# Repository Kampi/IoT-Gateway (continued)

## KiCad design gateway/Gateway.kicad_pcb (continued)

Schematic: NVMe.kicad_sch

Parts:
C1501, C1502, C1511: 10u; C_0805_2012Metric; mouser# 581-KGM21FS61E106KU
C1503, C1505, C1508, C1509: 100n; C_0805_2012Metric; mouser# 581-08055C104K4Z4A
C1504: 68n; C_0805_2012Metric; mouser# 581-08055C683K4T4A
C1506: 150p; C_0805_2012Metric; mouser# 581-08051U151JAT2A
C1507: 470u; CP_Elec_6.3x7.7; mouser# 667-EEE-FNJ471XUL
C1510: 33p; C_0805_2012Metric; mouser# 581-08053C330KAT2A
D1501: STPS3L60U; D_SMB; mouser# 511-STPS3L60U
H1501: Spacer; 9774025151R; mouser# 710-9774025151R
IC1501: ST1S14PHR; HSOP-8-1EP_3.9x4.9mm_P1.27mm_EP2.41x3.1mm; mouser# 511-ST1S14PHR
L1501: 10u; L_Wuerth_HCI-7050; mouser# 710-744314101
R1501, R1503: 100k; R_0805_2012Metric; mouser# 603-RT0805FRE13100KL
R1502: 100k; R_0805_2012Metric; mouser# 603-RT0805FRE13100KL; not fitted
R1504: 82k5; R_0805_2012Metric; mouser# 652-CR0805FX-8252ELF
R1505: 48k7; R_0805_2012Metric; mouser# 652-CR0805FX-4872ELF
R1506: 4k7; R_0805_2012Metric; mouser# 652-CR0805-JW-472ELF
TP1501, TP1502: TestPoint_Pad_1.0x1.0mm
X1501: SSD; MDT420M03001; mouser# 523-MDT420M03001

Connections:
+1V8: R1501.2, R1506.1; also elsewhere on the board
/Project Architecture/NVMe/PCIe.CLK_N: X1501.53 (REFCLKn); also elsewhere on the board
/Project Architecture/NVMe/PCIe.CLK_P: X1501.55 (REFCLKp); also elsewhere on the board
/Project Architecture/NVMe/PCIe.RX_N: X1501.41 (PERn0/SATA-B+); also elsewhere on the board
/Project Architecture/NVMe/PCIe.RX_P: X1501.43 (PERp0/SATA-B-); also elsewhere on the board
/Project Architecture/NVMe/PCIe.TX_N: X1501.47 (PETn0/SATA-A-); also elsewhere on the board
/Project Architecture/NVMe/PCIe.TX_P: X1501.49 (PETp0/SATA-A+); also elsewhere on the board
/Project Architecture/NVMe/PCIe.~CLK-REQ: X1501.50 (~PERST); also elsewhere on the board
/Project Architecture/NVMe/PCIe.~RST: X1501.52 (~CLKREQ); also elsewhere on the board
/Project Architecture/NVMe/SSD-Power-Enable: IC1501.5 (EN2), R1501.1, R1502.2; also elsewhere on the board
/Project Architecture/NVMe/V_{SSD}: C1506.1, C1507.1, C1508.1, C1509.1, C1510.1, C1511.1, L1501.2, R1504.1, TP1502.1 (1_1), X1501.2 (3.3V), X1501.4 (3.3V), X1501.12 (3.3V), X1501.14 (3.3V), X1501.16 (3.3V), X1501.18 (3.3V), X1501.70 (3.3V), X1501.72 (3.3V), X1501.74 (3.3V)
/Project Architecture/NVMe/~CTRL_WAKE1_MICO: R1506.2, X1501.54 (~PEWAKE); also elsewhere on the board
GND: C1501.2, C1502.2, C1503.2, C1504.2, C1507.2, C1508.2, C1509.2, C1510.2, C1511.2, D1501.2 (A), IC1501.6 (GND), IC1501.9 (EP), R1502.1, R1503.1, R1505.2, X1501.1 (GND), X1501.3 (GND), X1501.9 (GND), X1501.15 (GND), X1501.21 (GND), X1501.27 (GND), X1501.33 (GND), X1501.39 (GND), X1501.45 (GND), X1501.51 (GND), X1501.57 (GND), X1501.71 (GND), X1501.73 (GND), X1501.75 (GND); also elsewhere on the board
unnamed: C1505.2, D1501.1 (K), IC1501.8 (SW), L1501.1
unnamed: C1505.1, IC1501.1 (BOOT)
unnamed: C1506.2, IC1501.4 (FB), R1504.2, R1505.1, TP1501.1 (1_1)
unnamed: IC1501.3 (~EN1), R1503.2
V_{In}: C1501.1, C1502.1, C1503.1, C1504.1, IC1501.7 (VIN); also elsewhere on the board

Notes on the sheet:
[${#}] ${TITLE}
LAYOUT NOTE: Add support for the Key M 2230 standard.
LAYOUT NOTE: Place close to M.2 connector.
DESIGN NOTE: Selected for ~3.28 V.
DESIGN NOTE: Enabled by default.

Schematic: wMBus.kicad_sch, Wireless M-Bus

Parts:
AE1301: wM-Bus-Antenna
C1301, C1302: 1u; C_0805_2012Metric; mouser# 581-08053G105MAT2A
C1303, C1304: 100n; C_0805_2012Metric; mouser# 581-08055C104K4Z4A
IC1301: TLV75733PDBV; SOT-23-5; mouser# 595-TLV75733PDYDR
IC1302: 74LVC1G07; SOT-353_SC-70-5; mouser# 771-74LVC1G07GW-G
IC1303: TXB0102DCU; VSSOP-8_2.3x2mm_P0.5mm; mouser# 595-TXB0102DCUR
LED1301: wM-Bus; LED_0805_2012Metric; mouser# 749-SM0805YC
M1301: iM891A-XL
MP1301: SLP3-300-100-F; mouser# 749-SLP3-300-100-F
R1301: 10k; R_0805_2012Metric; mouser# 652-CR0805FX-1002ELF; not fitted
R1302: 68R; R_0805_2012Metric; mouser# 652-CR0805JW-680ELF
R1303, R1304, R1305, R1306: 0R; R_0805_2012Metric; mouser# 652-CR0805-J/-000ELF
R1307: 10k; R_0805_2012Metric; mouser# 652-CR0805FX-1002ELF
TP1301, TP1302, TP1303: TestPoint_Pad_1.0x1.0mm

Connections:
+1V8: C1303.1, IC1302.5 (VCC), IC1303.3 (VCCA), IC1303.6 (OE); also elsewhere on the board
+5V: C1301.2, IC1301.1 (IN); also elsewhere on the board
/Project Architecture/System on Module/wM-Bus-Power-Enable: IC1301.3 (EN), R1301.1, TP1301.1 (1_1); also elsewhere on the board
/Project Architecture/System on Module/wM-Bus.Reset: IC1302.2, TP1303.1 (1_1); also elsewhere on the board
/Project Architecture/System on Module/wM-Bus.RxD: R1303.1; also elsewhere on the board
/Project Architecture/System on Module/wM-Bus.TxD: R1304.1; also elsewhere on the board
/Project Architecture/wMBus/+3V3: C1302.2, C1304.1, IC1301.5 (OUT), IC1303.7 (VCCB), LED1301.2 (A), M1301.29 (VDD), R1307.1, TP1302.1 (1_1)
GND: C1301.1, C1302.1, C1303.2, C1304.2, IC1301.2 (GND), IC1302.3 (GND), IC1303.2 (GND), M1301.5 (GND), M1301.15 (GND), M1301.17 (GND), M1301.24 (GND), M1301.28 (GND), M1301.30 (GND), M1301.31 (GND), M1301.32 (GND), M1301.33 (GND), M1301.34 (GND), M1301.35 (GND), R1301.2, R1302.2; also elsewhere on the board
unnamed: IC1303.5 (A1), R1303.2
unnamed: IC1303.4 (A2), R1304.2
unnamed: IC1303.8 (B1), R1305.1
unnamed: IC1303.1 (B2), R1306.1
unnamed: LED1301.1 (K), R1302.1
unnamed: M1301.18 (RxD), R1306.2
unnamed: M1301.19 (TxD), R1305.2
unnamed: IC1302.4, M1301.25 (~RESET), R1307.2

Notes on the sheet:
[${#}] ${TITLE}
DESIGN NOTE: Use version with on-board antenna connector.
Power supply

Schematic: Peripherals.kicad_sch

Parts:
C1401: 100n; C_0805_2012Metric; mouser# 581-08055C104K4Z4A; not fitted
C1402, C1403, C1404, C1405, C1406, C1407, C1408, C1409, C1410: 100n; C_0805_2012Metric; mouser# 581-08055C104K4Z4A
IC1401: ATECC608B-SSHDA; SOIC-8_3.9x4.9mm_P1.27mm; mouser# 579-TECC608B-SSHDA-B; not fitted
IC1402: TUSB320; Texas_X2QFN-12_1.6x1.6mm_P0.4mm; mouser# 595-TUSB320LIRWBR
IC1403: TXS0108EPW; TSSOP-20_4.4x6.5mm_P0.65mm; mouser# 595-TXS0108EPWR
IC1404, IC1406: TXS0102DCU; VSSOP-8_2.3x2mm_P0.5mm; mouser# 595-TXS0102DCUR
IC1405: TXB0102DCU; VSSOP-8_2.3x2mm_P0.5mm; mouser# 595-TXB0102DCUR
R1401: 887k; R_0805_2012Metric; mouser# 652-CR0805FX-8873ELF
R1402: 1k8; R_0805_2012Metric; mouser# 652-CR0805JW-182ELF
R1403: 4k7; R_0805_2012Metric; mouser# 652-CR0805-JW-472ELF
R1404, R1405, R1406, R1407: 3k3; R_0805_2012Metric; mouser# 652-CR0805-JW-332ELF; not fitted
TP1401: TestPoint_Pad_1.0x1.0mm
X1401: OTG; USB4110; mouser# 640-USB4110-GF-A
X1402: GPIO; MSTBA_2,5_10-G-5,08_1x10_P5.08mm_Horizontal; mouser# 651-1757323; not fitted
X1403, X1405: I2C; MSTBA_2,5_4-G-5,08_1x04_P5.08mm_Horizontal; mouser# 651-1776524; not fitted
X1404: CAN; MSTBA_2,5_4-G-5,08_1x04_P5.08mm_Horizontal; mouser# 651-1776524; not fitted

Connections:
+1V8: C1403.1, C1405.1, C1406.1, C1407.1, IC1403.2 (VCCA), IC1403.10 (OE), IC1404.3 (VCCA), IC1404.6 (OE), IC1405.3 (VCCA), IC1405.6 (OE), IC1406.3 (VCCA), IC1406.6 (OE), R1403.1; also elsewhere on the board
+3V3: C1401.2, C1402.2, IC1401.8 (VCC), IC1402.12 (VDD); also elsewhere on the board
/Project Architecture/Battery/I2C.SCL: IC1401.6 (SCL), IC1404.4 (A2), IC1406.4 (A2); also elsewhere on the board
/Project Architecture/Battery/I2C.SDA: IC1401.5 (SDA), IC1404.5 (A1), IC1406.5 (A1); also elsewhere on the board
/Project Architecture/Peripherals/CAN.Rx: IC1405.4 (A2); also elsewhere on the board
/Project Architecture/Peripherals/CAN.Tx: IC1405.5 (A1); also elsewhere on the board
/Project Architecture/Peripherals/GPIO.Num0: IC1403.1 (A1); also elsewhere on the board
/Project Architecture/Peripherals/GPIO.Num1: IC1403.3 (A2); also elsewhere on the board
/Project Architecture/Peripherals/GPIO.Num2: IC1403.4 (A3); also elsewhere on the board
/Project Architecture/Peripherals/GPIO.Num3: IC1403.5 (A4); also elsewhere on the board
/Project Architecture/Peripherals/GPIO.Num4: IC1403.6 (A5); also elsewhere on the board
/Project Architecture/Peripherals/GPIO.Num5: IC1403.7 (A6); also elsewhere on the board
/Project Architecture/Peripherals/GPIO.Num6: IC1403.8 (A7); also elsewhere on the board
/Project Architecture/Peripherals/GPIO.Num7: IC1403.9 (A8); also elsewhere on the board
/Project Architecture/Peripherals/USB.D_N: X1401.A6 (D+), X1401.B6 (D+); also elsewhere on the board
/Project Architecture/Peripherals/USB.D_P: X1401.A7 (D-), X1401.B7 (D-); also elsewhere on the board
/Project Architecture/Peripherals/USB.ID: IC1402.9 (ID), R1403.2, TP1401.1 (1_1); also elsewhere on the board
/Project Architecture/Peripherals/USB.VBUS: R1401.1, X1401.A4 (VBUS), X1401.A9 (VBUS), X1401.B4 (VBUS), X1401.B9 (VBUS); also elsewhere on the board
GND: C1401.1, C1402.1, C1403.2, C1404.2, C1405.2, C1406.2, C1407.2, C1408.2, C1409.2, C1410.2, IC1401.4 (GND), IC1402.10 (GND), IC1403.11 (GND), IC1404.2 (GND), IC1405.2 (GND), IC1406.2 (GND), R1402.2, X1401.A1 (GND), X1401.A12 (GND), X1401.B1 (GND), X1401.B12 (GND), X1401.SH (SHIELD), X1402.10, X1403.4, X1404.4, X1405.4; also elsewhere on the board
unnamed: IC1402.1 (CC1), X1401.A5 (CC1)
unnamed: IC1402.2 (CC2), X1401.B5 (CC2)
unnamed: IC1402.4 (VBUS_DET), R1401.2
unnamed: IC1402.11 (~EN), R1402.1
unnamed: IC1403.20 (B1), X1402.2
unnamed: IC1403.18 (B2), X1402.3
unnamed: IC1403.17 (B3), X1402.4
unnamed: IC1403.16 (B4), X1402.5
unnamed: IC1403.15 (B5), X1402.6
unnamed: IC1403.14 (B6), X1402.7
unnamed: IC1403.13 (B7), X1402.8
unnamed: IC1403.12 (B8), X1402.9
unnamed: C1404.1, IC1403.19 (VCCB), X1402.1
unnamed: IC1404.8 (B1), R1404.2, X1403.2
unnamed: IC1404.1 (B2), R1406.2, X1403.3
unnamed: C1408.1, IC1404.7 (VCCB), R1404.1, R1406.1, X1403.1
unnamed: IC1405.8 (B1), X1404.2
unnamed: IC1405.1 (B2), X1404.3
unnamed: C1409.1, IC1405.7 (VCCB), X1404.1
unnamed: IC1406.8 (B1), R1405.2, X1405.2
unnamed: IC1406.1 (B2), R1407.2, X1405.3
unnamed: C1410.1, IC1406.7 (VCCB), R1405.1, R1407.1, X1405.1

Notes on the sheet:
USB OTG
Extension interfaces
[${#}] ${TITLE}
DESIGN NOTE: The device supports 1.8 V I/O levels.
Cryptographic Coprocessor

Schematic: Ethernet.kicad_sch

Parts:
C1601: 470u; CP_Elec_6.3x7.7; mouser# 667-EEE-FNJ471XUL
C1602, C1603: 4n7; C_1206_3216Metric; mouser# 80-C1206C472KFRACTU
C1604: 10n; C_0805_2012Metric; mouser# 581-08052C103MAT2A
C1605, C1606: 100n; C_0805_2012Metric; mouser# 581-08055C104K4Z4A
C1607: 1n; C_1206_3216Metric; mouser# 581-1206GC102K
D1601, D1602, D1603, D1604: SS36; D_SMA; mouser# 625-SS36-E3
IC1601: TLP293; TLP293(TPL,E; mouser# 757-TLP293(Y-TPLE
M1601: Ag5400; mouser# 480-AG5412
R1601, R1602: R_0805_2012Metric; not fitted
R1603: 1k8; R_0805_2012Metric; mouser# 652-CR0805JW-182ELF; not fitted
R1604, R1605: 470R; R_0805_2012Metric; mouser# 652-CR0805JW-471ELF
R1606: 1M; R_2010_5025Metric; mouser# 71-CRMA2010AF1M00DKF
TP1601, TP1602, TP1603, TP1604, TP1605: TestPoint_Pad_1.0x1.0mm
X1601: Ethernet; RJ45_Pulse_JK00177NL_Horizontal; mouser# 673-JK0-0177NL

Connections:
+1V8: R1603.1; also elsewhere on the board
+3V3: R1604.1, R1605.1; also elsewhere on the board
/Project Architecture/Ethernet/AT-DET: IC1601.4, R1603.2; also elsewhere on the board
/Project Architecture/Ethernet/Ethernet.LED-Green: X1601.14 (LED2-); also elsewhere on the board
/Project Architecture/Ethernet/Ethernet.LED-Yellow: X1601.16 (LED1+); also elsewhere on the board
/Project Architecture/Ethernet/Ethernet.TRD0_N: X1601.10 (MX1-); also elsewhere on the board
/Project Architecture/Ethernet/Ethernet.TRD0_P: X1601.11 (MX1+); also elsewhere on the board
/Project Architecture/Ethernet/Ethernet.TRD1_N: X1601.5 (MX2-); also elsewhere on the board
/Project Architecture/Ethernet/Ethernet.TRD1_P: X1601.4 (MX2+); also elsewhere on the board
/Project Architecture/Ethernet/Ethernet.TRD2_N: X1601.2 (MX3-); also elsewhere on the board
/Project Architecture/Ethernet/Ethernet.TRD2_P: X1601.3 (MX3+); also elsewhere on the board
/Project Architecture/Ethernet/Ethernet.TRD3_N: X1601.9 (MX4-); also elsewhere on the board
/Project Architecture/Ethernet/Ethernet.TRD3_P: X1601.8 (MX4+); also elsewhere on the board
/Project Architecture/Ethernet/PoE: C1601.1, M1601.8 (V_{DC}+), R1601.1, TP1601.1 (1_1); also elsewhere on the board
/Project Architecture/Ethernet/PoE-A: D1601.1 (K), D1603.1 (K), TP1604.1 (1_1), X1601.17 (VDC1+), X1601.18 (VDC1-)
/Project Architecture/Ethernet/PoE-B: D1602.2 (A), D1604.2 (A), TP1605.1 (1_1), X1601.19 (VDC2+), X1601.20 (VDC2-)
Earth: C1607.1, R1606.1, X1601.SH
GND: C1601.2, C1602.1, C1603.1, C1605.2, C1606.2, C1607.2, IC1601.3, M1601.7 (V_{DC}-), M1601.10 (V_{DC}-), R1602.2, R1606.2; also elsewhere on the board
unnamed: C1603.2, C1604.2, D1601.2 (A), D1602.1 (K), M1601.2 (V_{IN}-), TP1603.1 (1_1)
unnamed: C1602.2, C1604.1, D1603.2 (A), D1604.1 (K), IC1601.1, M1601.1 (V_{IN}+), TP1602.1 (1_1)
unnamed: M1601.9 (ADJ), R1601.2, R1602.1
unnamed: IC1601.2, M1601.3 (AT-DET)
unnamed: R1605.2, X1601.15 (LED1-)
unnamed: R1604.2, X1601.13 (LED2+)
unnamed: C1605.1, X1601.6 (MXCT2), X1601.12 (MXCT1)
unnamed: C1606.1, X1601.1 (MXCT3), X1601.7 (MXCT4)

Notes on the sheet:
LAYOUT NOTE: As close as possible to the RJ45 jack.
[${#}] ${TITLE}
Power-over-Ethernet+ Converter
DESIGN NOTE: Use one of these to increase / decrease the output voltage (see the datasheet).

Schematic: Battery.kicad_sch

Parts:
BAT801: Backup Battery; 1043; mouser# 534-1043
C801, C805: 10u; C_0805_2012Metric; mouser# 581-KGM21FS61E106KU
C802, C803: 2u2; C_0805_2012Metric; mouser# 963-T21GCB7225MTPA1J
C804: 47n; C_0805_2012Metric; mouser# 581-08053C473K4T2A
C806: 220p; C_0805_2012Metric; mouser# 581-08052C221JAT2A
C807, C808: 100n; C_0805_2012Metric; mouser# 581-08055C104K4Z4A
C809: 4u7; C_0805_2012Metric; mouser# 581-08055D475KAT4A; not fitted
IC801: BQ25300; WQFN-16-1EP_3x3mm_P0.5mm_EP1.68x1.68mm; mouser# 595-BQ25300RTER
IC802: TPS22965; WSON-8-1EP_2x2mm_P0.5mm_EP0.9x1.6mm_ThermalVias; mouser# 595-TPS22965NTDSGRQ1
IC803: MAX17048; TDFN-8-1EP_2x2mm_P0.5mm_EP0.8x1.2mm; mouser# 700-MAX17048G+T10
IC804: BQ297xy; WSON-6_1.5x1.5mm_P0.5mm; mouser# 595-BQ29704DSER
L801: 2u2; L_Wuerth_WE-PD-Typ-7345; mouser# 710-744777002
Q801, Q802: CSD16301Q2; Texas_DQK; mouser# 595-CSD16301Q2
R801, R804, R811: 100k; R_0805_2012Metric; mouser# 603-RT0805FRE13100KL; not fitted
R802: 0R; R_0805_2012Metric; mouser# 652-CR0805-J/-000ELF
R803: 18k; R_0805_2012Metric; mouser# 652-CR0805FX-1802ELF
R805: 100k; R_0805_2012Metric; mouser# 603-RT0805FRE13100KL
R806: 4k53; R_0805_2012Metric; mouser# 652-CR0805FX-4531ELF
R807: 22k6; R_0805_2012Metric; mouser# 603-AC0805FR-0722K6L
R808: 2k2; R_0805_2012Metric; mouser# 652-CR0805JW-222ELF
R809, R810: 5M1; R_0805_2012Metric; mouser# 603-RC0805JR-075M1L
R812: 330R; R_0805_2012Metric; mouser# 652-CR0805JW-331ELF
TH801: 10k; R_0805_2012Metric; mouser# 652-CR0805FX-1002ELF; not fitted
TP801, TP802, TP803, TP804: TestPoint_Pad_1.0x1.0mm

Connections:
+1V8: R804.1, R811.2; also elsewhere on the board
/Project Architecture/Battery/Battery-Backup-Enable: IC802.3 (ON), R805.2; also elsewhere on the board
/Project Architecture/Battery/Battery-Charge-Enable: IC801.6 (~EN), R801.1; also elsewhere on the board
/Project Architecture/Battery/I2C.SCL: IC803.7 (SCL); also elsewhere on the board
/Project Architecture/Battery/I2C.SDA: IC803.8 (SDA); also elsewhere on the board
/Project Architecture/Battery/REGN: C802.1, IC801.2 (REGN), R806.1
/Project Architecture/Battery/V_{Batt}: IC802.7 (VOUT), IC802.8 (VOUT), TP803.1 (1_1); also elsewhere on the board
/Project Architecture/Battery/~Battery-Alert: IC803.5 (~ALERT), R811.1, TP804.1 (1_1); also elsewhere on the board
/Project Architecture/Battery/~Battery-Charge: IC801.3 (STAT), R804.2, TP801.1 (1_1); also elsewhere on the board
GND: C801.2, C802.2, C803.2, C805.2, C806.2, C807.2, IC801.5 (POL), IC801.11 (GND), IC801.12 (GND), IC801.17 (GND), IC802.5 (GND), IC802.9 (PAD), IC803.1 (CTG), IC803.4 (GND), IC803.6 (QSTRT), IC803.9 (EP), Q801.4 (S), Q801.7 (S), R801.2, R802.2, R803.2, R805.1, R807.2, R808.2, R809.1, TH801.2; also elsewhere on the board
unnamed: BAT801.1 (+), C805.1, C807.1, C809.1, IC801.10 (BAT), IC802.1 (VIN), IC802.2 (VIN), IC802.4 (VBIAS), IC803.2 (CELL), IC803.3 (VDD), L801.2, R812.1
unnamed: BAT801.2 (-), C808.2, C809.2, IC804.4 (VSS), Q802.4 (S), Q802.7 (S), R810.1
unnamed: C804.1, IC801.13 (SW), IC801.14 (SW), L801.1
unnamed: C804.2, IC801.15 (BTST)
unnamed: IC801.4 (ICHG), R803.1
unnamed: C801.1, IC801.16 (PMID)
unnamed: IC801.7 (TS), R806.2, R807.1, TH801.1, TP802.1 (1_1)
unnamed: IC801.9 (VSET), R802.1
unnamed: C806.1, IC802.6 (CT)
unnamed: C808.1, IC804.5 (BAT), R812.2
unnamed: IC804.2 (Cout), Q801.3 (G), R809.2
unnamed: IC804.3 (Dout), Q802.3 (G), R810.2
unnamed: IC804.6 (V-), R808.1
unnamed: Q801.1 (D), Q801.2 (D), Q801.5 (D), Q801.6 (D), Q801.8 (D), Q802.1 (D), Q802.2 (D), Q802.5 (D), Q802.6 (D), Q802.8 (D)
V_{In}: C803.1, IC801.1 (VBUS); also elsewhere on the board

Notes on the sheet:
DESIGN NOTE: Charge current set to ~2.2 A.
DESIGN NOTE: Charge voltage set to 4.05 V.
DESIGN NOTE: Charge status indication output. This pin is an open drain output. Connect this pin to REGN via a current limiting resistor and LED. The STAT pin indicates charger status as: • Charge in progress: STAT pin is pulled LOW • Charge completed, charge disabled by EN: STAT pin is OPEN • Faul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
Battery Protection
[${#}] ${TITLE}
DESIGN NOTE: Can be used to shutdown the system at 3.2 V.
LiPo Gauge
DESIGN NOTE: Can be used for high load peaks.
Battery Charger
LAYOUT NOTE: Place as near as possible to BAT and VSS.
DESIGN NOTE: Selected for 0°C to 45°C.

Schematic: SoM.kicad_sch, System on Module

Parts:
BT901: Backup; 3030TR; mouser# 534-3030TR
C901: 100n; C_0805_2012Metric; mouser# 581-08055C104K4Z4A
H901, H903: Spacer; 9774025151R; mouser# 710-9774025151R
H902: MountingHole; MountingHole_3.2mm_M3_Pad_Via
JP901: Recovery; PinHeader_2x01_P2.54mm_Vertical; not fitted
LED901: Ready; LED_0805_2012Metric; mouser# 749-SM0805YC
MP901: SLP3-300-100-F; mouser# 749-SLP3-300-100-F
Q901: BSS138; SOT-23-3; mouser# 512-BSS138
R901, R907: 10k; R_0805_2012Metric; mouser# 652-CR0805FX-1002ELF
R902: 1k5; R_0805_2012Metric; mouser# 652-CR0805FX-1501ELF
R903, R904, R908: 1k8; R_0805_2012Metric; mouser# 652-CR0805JW-182ELF
R905, R906, R910: 10k; R_0805_2012Metric; mouser# 652-CR0805FX-1002ELF; not fitted
R909, R911: R_0805_2012Metric; not fitted
R912: 0R; R_0805_2012Metric; mouser# 652-CR0805-J/-000ELF
SW901: Reset; TS11; mouser# 179-TS1167443260RAD
SW902: On / Off; TS11; mouser# 179-TS1167443260RAD
X901: UART; PinHeader_1x03_P2.54mm_Vertical; not fitted
X902: SoM; 2309409-2; mouser# 571-2309409-2

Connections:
+1V8: R903.1, R904.1, R905.1, R906.1, R907.1, R910.1; also elsewhere on the board
+5V: LED901.2 (A), X902.251, X902.253, X902.255, X902.257, X902.259; also elsewhere on the board
/Project Architecture/Battery/Battery-Backup-Enable: X902.114; also elsewhere on the board
/Project Architecture/Battery/Battery-Charge-Enable: X902.42; also elsewhere on the board
/Project Architecture/Battery/I2C.SCL: R904.2, X902.14; also elsewhere on the board
/Project Architecture/Battery/I2C.SDA: R903.2, X902.12; also elsewhere on the board
/Project Architecture/Battery/~Battery-Alert: X902.46; also elsewhere on the board
/Project Architecture/Battery/~Battery-Charge: X902.44; also elsewhere on the board
/Project Architecture/Ethernet/AT-DET: X902.48; also elsewhere on the board
/Project Architecture/Ethernet/Ethernet.LED-Green: X902.237; also elsewhere on the board
/Project Architecture/Ethernet/Ethernet.LED-Yellow: X902.235; also elsewhere on the board
/Project Architecture/Ethernet/Ethernet.TRD0_N: X902.227; also elsewhere on the board
/Project Architecture/Ethernet/Ethernet.TRD0_P: X902.225; also elsewhere on the board
/Project Architecture/Ethernet/Ethernet.TRD1_N: X902.231; also elsewhere on the board
/Project Architecture/Ethernet/Ethernet.TRD1_P: X902.233; also elsewhere on the board
/Project Architecture/Ethernet/Ethernet.TRD2_N: X902.241; also elsewhere on the board
/Project Architecture/Ethernet/Ethernet.TRD2_P: X902.239; also elsewhere on the board
/Project Architecture/Ethernet/Ethernet.TRD3_N: X902.245; also elsewhere on the board
/Project Architecture/Ethernet/Ethernet.TRD3_P: X902.247; also elsewhere on the board
/Project Architecture/LoRa/LoRa-Power-Enable: X902.30; also elsewhere on the board
/Project Architecture/LoRa/LoRa.D_N: X902.181; also elsewhere on the board
/Project Architecture/LoRa/LoRa.D_P: X902.183; also elsewhere on the board
/Project Architecture/LoRa/LoRa.Reset: X902.185; also elsewhere on the board
/Project Architecture/NVMe/PCIe.CLK_N: X902.226; also elsewhere on the board
/Project Architecture/NVMe/PCIe.CLK_P: X902.228; also elsewhere on the board
/Project Architecture/NVMe/PCIe.RX_N: X902.236; also elsewhere on the board
/Project Architecture/NVMe/PCIe.RX_P: X902.234; also elsewhere on the board
/Project Architecture/NVMe/PCIe.TX_N: X902.238; also elsewhere on the board
/Project Architecture/NVMe/PCIe.TX_P: X902.240; also elsewhere on the board
/Project Architecture/NVMe/PCIe.~CLK-REQ: X902.151; also elsewhere on the board
/Project Architecture/NVMe/PCIe.~RST: X902.244; also elsewhere on the board
/Project Architecture/NVMe/SSD-Power-Enable: X902.187; also elsewhere on the board
/Project Architecture/NVMe/~CTRL_WAKE1_MICO: X902.252; also elsewhere on the board
/Project Architecture/Peripherals/CAN.Rx: X902.22; also elsewhere on the board
/Project Architecture/Peripherals/CAN.Tx: X902.20; also elsewhere on the board
/Project Architecture/Peripherals/GPIO.Num0: X902.21; also elsewhere on the board
/Project Architecture/Peripherals/GPIO.Num1: X902.19; also elsewhere on the board
/Project Architecture/Peripherals/GPIO.Num2: X902.17; also elsewhere on the board
/Project Architecture/Peripherals/GPIO.Num3: X902.96; also elsewhere on the board
/Project Architecture/Peripherals/GPIO.Num4: X902.94; also elsewhere on the board
/Project Architecture/Peripherals/GPIO.Num5: X902.91; also elsewhere on the board
/Project Architecture/Peripherals/GPIO.Num6: X902.93; also elsewhere on the board
/Project Architecture/Peripherals/GPIO.Num7: X902.95; also elsewhere on the board
/Project Architecture/Peripherals/USB.D_N: X902.163; also elsewhere on the board
/Project Architecture/Peripherals/USB.D_P: X902.165; also elsewhere on the board
/Project Architecture/Peripherals/USB.ID: X902.161; also elsewhere on the board
/Project Architecture/Peripherals/USB.VBUS: X902.159; also elsewhere on the board
/Project Architecture/Power Input/ADC.ADC_1: X902.2; also elsewhere on the board
/Project Architecture/Power Input/ADC.ADC_2: X902.4
/Project Architecture/Power Input/ADC.ADC_3: X902.6
/Project Architecture/Power Input/ADC.ADC_4: X902.8
/Project Architecture/Power Input/Input-Status: X902.38; also elsewhere on the board
/Project Architecture/Power/PWR_1V8_MOCI: R912.2; also elsewhere on the board
/Project Architecture/Power/PowerMux-Status: X902.210; also elsewhere on the board
/Project Architecture/Power/SoM-Power-Enable: X902.254; also elsewhere on the board
/Project Architecture/System on Module/Console-RxD: X901.1, X902.129
/Project Architecture/System on Module/Console-TxD: X901.3, X902.131
/Project Architecture/System on Module/Ready: Q901.1 (G), R901.1, X902.206
/Project Architecture/System on Module/Thread-Power-Enable: X902.36; also elsewhere on the board
/Project Architecture/System on Module/Thread.Boot: X902.112; also elsewhere on the board
/Project Architecture/System on Module/Thread.CTS: X902.202; also elsewhere on the board
/Project Architecture/System on Module/Thread.RTS: X902.198; also elsewhere on the board
/Project Architecture/System on Module/Thread.Reset: X902.108; also elsewhere on the board
/Project Architecture/System on Module/Thread.RxD: X902.196; also elsewhere on the board
/Project Architecture/System on Module/Thread.TxD: X902.200; also elsewhere on the board
/Project Architecture/System on Module/Zigbee-Power-Enable: X902.32; also elsewhere on the board
/Project Architecture/System on Module/Zigbee.Boot: X902.106; also elsewhere on the board
/Project Architecture/System on Module/Zigbee.Reset: X902.104; also elsewhere on the board
/Project Architecture/System on Module/Zigbee.RxD: X902.147; also elsewhere on the board
/Project Architecture/System on Module/Zigbee.TxD: X902.149; also elsewhere on the board
/Project Architecture/System on Module/wM-Bus-Power-Enable: X902.34; also elsewhere on the board
/Project Architecture/System on Module/wM-Bus.Reset: X902.102; also elsewhere on the board
/Project Architecture/System on Module/wM-Bus.RxD: X902.137; also elsewhere on the board
/Project Architecture/System on Module/wM-Bus.TxD: X902.139; also elsewhere on the board
/Project Architecture/System on Module/~CTRL_FORCE_OFF_MOC: R911.2, X902.250
/Project Architecture/System on Module/~CTRL_PWR_BTN_MICO: SW902.1, X902.248
/Project Architecture/System on Module/~CTRL_RECOVERY_MICO: JP901.1 (A), X902.246
/Project Architecture/System on Module/~CTRL_RESET_MICO: C901.1, R908.1, X902.260
/Project Architecture/System on Module/~CTRL_RESET_MOCI: R907.2, R909.2, X902.258
/Project Architecture/System on Module/~SoM-Peripheral-Reset: R909.1
GND: BT901.2 (-), C901.2, H902.1 (1_1), JP901.2 (B), Q901.2 (S), R901.2, R911.1, SW901.2, SW901.SH (B), SW902.2, SW902.SH (B), X901.2, X902.11, X902.27, X902.39, X902.45, X902.51, X902.65, X902.71, X902.77, X902.83, X902.89, X902.97, X902.103, X902.109, X902.115, X902.121, X902.145, X902.167, X902.173, X902.179, X902.195, X902.209, X902.223, X902.229, X902.243, X902.SH; also elsewhere on the board
unnamed: BT901.1 (+), X902.249
unnamed: LED901.1 (K), R902.1
unnamed: Q901.3 (D), R902.2
unnamed: R905.2, X902.212
unnamed: R906.2, X902.216
unnamed: R908.2, SW901.1
unnamed: R910.2, X902.218
unnamed: R912.1, X902.214

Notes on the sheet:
DESIGN NOTE: Close this jumper before a power-up to boot into recovery mode.
DESIGN NOTE: max. 250 mA.
DESIGN NOTE: Long pulling down (>5 s) is shutting down the module. Short pulling down is turning on module from off state.
[${#}] ${TITLE}

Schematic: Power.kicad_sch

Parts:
C701, C703, C707, C715, C717, C723: 10u; C_0805_2012Metric; mouser# 581-KGM21FS61E106KU
C702, C719, C722: 1u; C_0805_2012Metric; mouser# 581-08053G105MAT2A
C704: 47n; C_0805_2012Metric; mouser# 581-08053C473K4T2A
C705, C706: 470n; C_0805_2012Metric; mouser# 581-KAF21KR71H474MU
C708: C_0805_2012Metric; not fitted
C709, C721: 100n; C_0805_2012Metric; mouser# 581-08055C104K4Z4A
C710: 22n; C_0805_2012Metric; mouser# 581-08052C223M4Z2A
C711, C713, C714, C716: 22u; C_0805_2012Metric; mouser# 963-MLAST21GBB5226MT
C712: 33p; C_0805_2012Metric; mouser# 581-08053C330KAT2A
C718: 10p; C_0805_2012Metric; mouser# 581-08053A100JAT2A
C720: 220u; CP_EIA-7343-31_Kemet-D; mouser# 80-T520D227M10ATE25
C724, C725: 1u; C_0805_2012Metric; mouser# 581-08053G105MAT2A; not fitted
D701: CMS05; M-FLAT-2; mouser# 757-CMS05TE12LQM
IC701: LM62460; RPH0016A; mouser# 595-LM62460RPHR
IC702: ADP1614ACPZ-650-R7; LFCSP-10; mouser# 584-ADP1614ACPZ650R7
IC703: TLV75733PDBV; SOT-23-5; mouser# 595-TLV75733PDYDR
IC704: TPS2121RUXT; RUX0012A; mouser# 595-TPS2121RUXT
IC705: TLV75733PDBV; SOT-23-5; mouser# 595-TLV75733PDBVT; not fitted
L701: 4u7; L_Coilcraft_XAL5030-XXX; mouser# 994-XAL5030-472MEC
L702: 2u2; L_Wuerth_WE-PD-Typ-7345; mouser# 710-744777002
Q701: BSS138; SOT-23-3; mouser# 512-BSS138
R701, R724: 0R; R_0805_2012Metric; mouser# 652-CR0805-J/-000ELF
R702, R706, R718, R721, R723: 10k; R_0805_2012Metric; mouser# 652-CR0805FX-1002ELF
R703: 66k5; R_0805_2012Metric; mouser# 603-RT0805BRD0766K5L
R704: 2k; R_0805_2012Metric; mouser# 652-CR0805FX-2001ELF
R705: 30k9; R_0805_2012Metric; mouser# 652-CR0805FX-3092ELF
R707: 100k; R_0805_2012Metric; mouser# 603-RT0805FRE13100KL
R708: 24k9; R_0805_2012Metric; mouser# 652-CR0805FX-2492ELF
R709: 4k99; R_0805_2012Metric; mouser# 652-CR0805FX-4991ELF
R710, R712: 23k7; R_0805_2012Metric; mouser# 603-RC0805FR-0723K7L
R711, R713: 5k36; R_0805_2012Metric; mouser# 667-ERA-6AEB5361V
R714: 22k1; R_0805_2012Metric; mouser# 603-RT0805BRD0722K1L
R715, R717: 93k1; R_0805_2012Metric; mouser# 603-RT0805BRD0793K1L
R716: 16k5; R_0805_2012Metric; mouser# 603-RT0805BRD0716K5L
R719: 1M; R_0805_2012Metric; mouser# 603-RC0805FR-071ML
R720: 23k2; R_0805_2012Metric; mouser# 603-RT0805BRD0723K2L
R722: 10k; R_0805_2012Metric; mouser# 652-CR0805FX-1002ELF; not fitted
TP701, TP702, TP703, TP705, TP706, TP707, TP708: TestPoint_Pad_1.0x1.0mm
TP704: TestPoint_Pad_1.0x1.0mm

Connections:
+1V8: C725.2, IC705.5 (OUT), R723.1, R724.2, TP708.1 (1_1); also elsewhere on the board
+3V3: C722.2, IC703.5 (OUT), TP705.1 (1_1); also elsewhere on the board
+5V: C719.2, C720.1, C723.1, C724.2, IC703.1 (IN), IC704.1 (OUT), IC704.8 (OUT), IC705.1 (IN), R721.1, TP704.1 (1_1); also elsewhere on the board
/Project Architecture/Battery/V_{Batt}: C701.1, IC702.3 (EN), IC702.8 (VIN), L701.1; also elsewhere on the board
/Project Architecture/Power/PWR_1V8_MOCI: R724.1; also elsewhere on the board
/Project Architecture/Power/PowerMux-Status: Q701.3 (D), R723.2, TP707.1 (1_1); also elsewhere on the board
/Project Architecture/Power/SoM-Power-Enable: IC703.3 (EN), IC705.3 (EN), R718.1, R722.1; also elsewhere on the board
GND: C701.2, C702.1, C703.1, C704.2, C705.1, C706.1, C707.1, C708.1, C710.2, C711.1, C712.2, C713.1, C714.1, C715.2, C716.1, C717.2, C719.1, C720.2, C721.2, C722.1, C723.2, C724.1, C725.1, IC701.1 (PGND), IC701.8 (AGND), IC701.12 (SYNC-MODE), IC701.15 (PGND), IC702.4 (GND), IC702.5 (GND), IC702.11 (EP), IC703.2 (GND), IC704.12 (GND), IC705.2 (GND), Q701.2 (S), R701.1, R703.2, R706.2, R708.2, R711.2, R713.2, R715.2, R717.2, R718.2, R720.2, R722.2; also elsewhere on the board
unnamed: C710.1, R704.2
unnamed: C718.2, R709.2
unnamed: D701.2 (A), IC702.6 (SW), IC702.7 (SW), L701.2
unnamed: C715.1, C717.1, D701.1 (K), IC704.2 (IN2), R705.1, R712.1, R714.1, TP703.1 (1_1)
unnamed: C708.2, C711.2, C713.2, C714.2, C716.2, IC701.5 (BIAS), IC704.7 (IN1), L702.2, R707.1, R709.1, R710.1, R716.1, TP702.1 (1_1)
unnamed: C709.1, IC701.3 (RBOOT), IC701.4 (CBOOT)
unnamed: C718.1, IC701.7 (FB), R707.2, R708.1
unnamed: IC701.10 (RESET), R702.2, TP701.1 (1_1)
unnamed: C702.2, IC701.6 (VCC), IC701.9 (RT)
unnamed: C709.2, IC701.16 (SW), L702.1
unnamed: IC701.11 (SpSp), R701.2
unnamed: IC702.9 (CLRES/FREQ), R703.1
unnamed: C712.1, IC702.1 (COMP), R704.1
unnamed: IC702.2 (FB), R705.2, R706.1
unnamed: C704.1, IC702.10 (SS)
unnamed: IC704.3 (CP2), R714.2, R715.1
unnamed: IC704.10 (ILIM), R720.1
unnamed: IC704.5 (OV1), R710.2, R711.1
unnamed: IC704.4 (OV2), R712.2, R713.1
unnamed: IC704.6 (PR1), R716.2, R717.1, R719.1
unnamed: C721.1, IC704.11 (SS)
unnamed: IC704.9 (ST), Q701.1 (G), R719.2, R721.2, TP706.1 (1_1)
V_{In}: C703.2, C705.2, C706.2, C707.2, IC701.2 (V_{In}), IC701.13 (EN), IC701.14 (V_{In}), R702.1; also elsewhere on the board

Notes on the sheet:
SoM supply
DESIGN NOTE: Selected for 4.35 A.
DESIGN NOTE: Set to NA when using the fixed output variant.
DESIGN NOTE: Set to 0R when using the fixed output variant.
DESIGN NOTE: IN2 selected at V < 4.88 V and IN1 selected at V > 4.96 V.
DESIGN NOTE: Power supply is designed for 5 V / 5 A (25 W).
Peripherals
[${#}] ${TITLE}
DESIGN NOTE: PR1 and CP2 must be greater than VREF (1.06 V) to enter XCOMP mode (5 us switchover time).
DESIGN NOTE: Set the CP2 threshold to 4.154 V.
DESIGN NOTE: Default is IN1.
DESIGN NOTE: Selected for 5.747 V.
DESIGN NOTE: Use the PowerMux-Status signal to detect a switch to the backup and enter a low power mode.
DESIGN NOTE: 780 V/s selected.
V_{Backup} power supply
DESIGN NOTE: Selected for 2 MHz.
DESIGN NOTE: Selected for ~5.09 V.
On-board peripherals power
Priority Power MUX

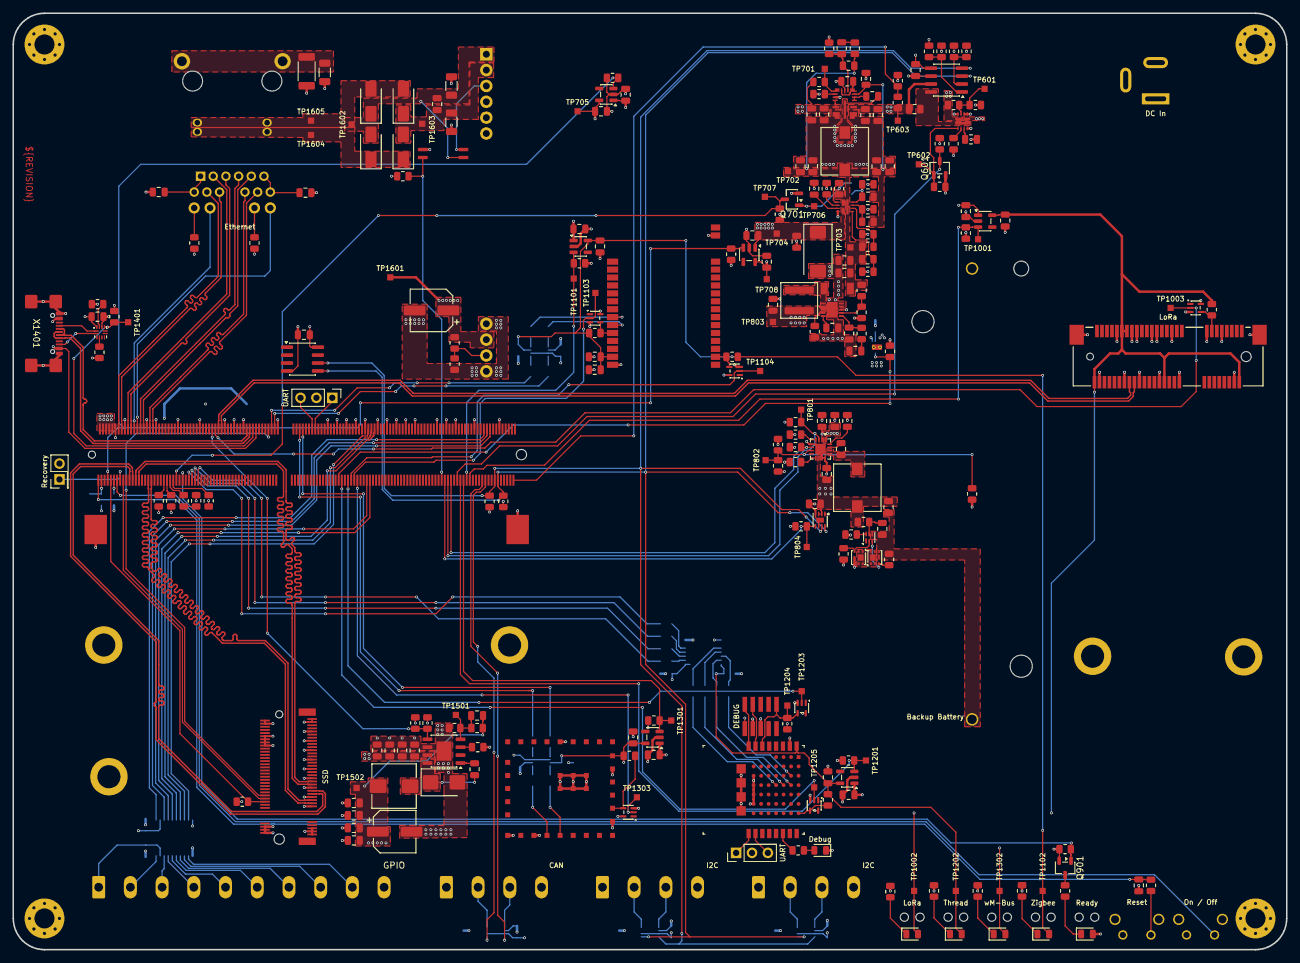
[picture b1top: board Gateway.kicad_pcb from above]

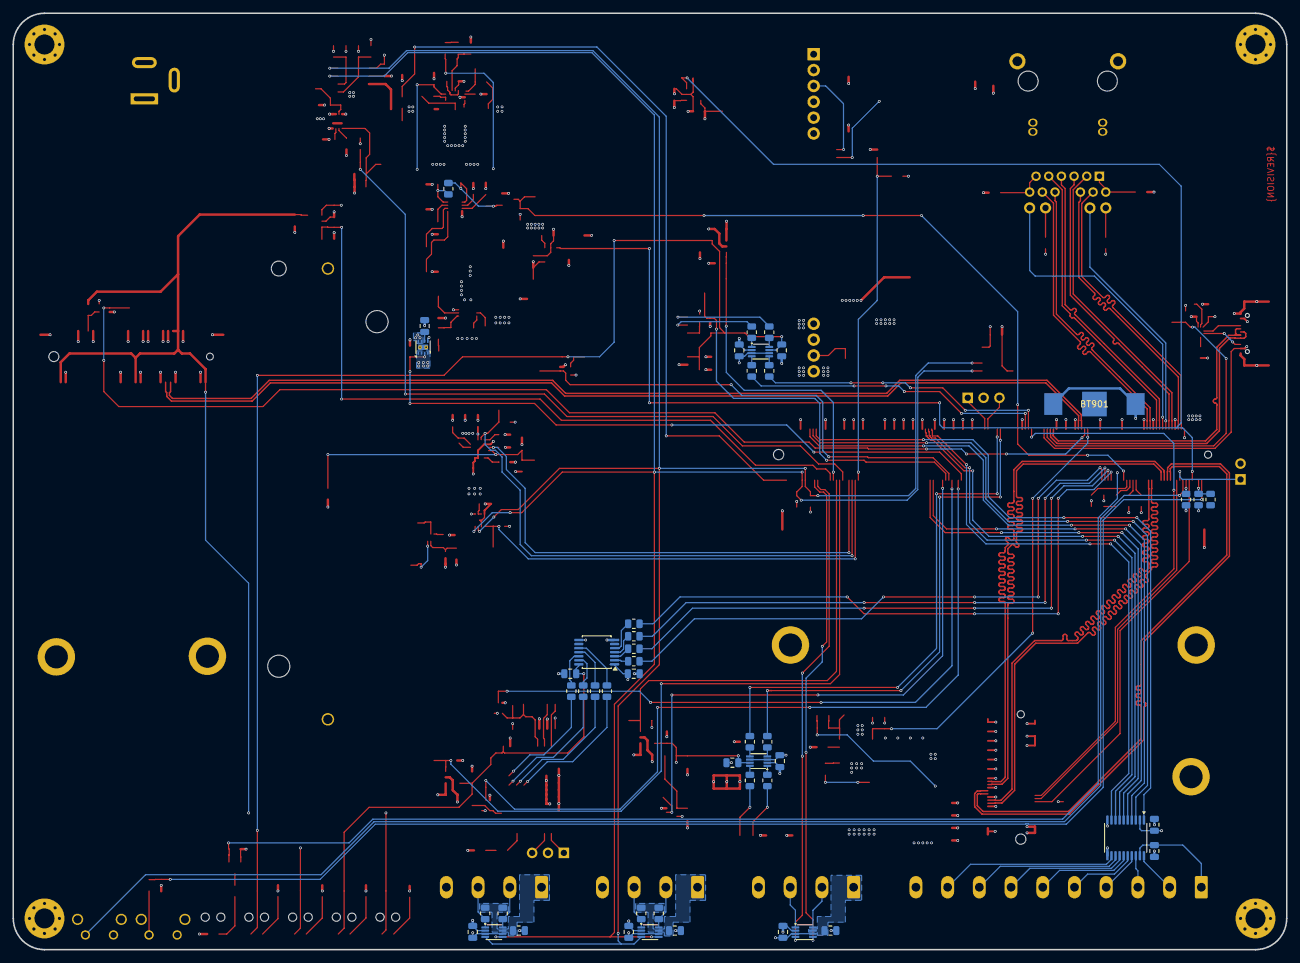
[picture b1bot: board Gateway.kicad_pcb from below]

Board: 4 copper layers, 204.0 x 150.0 mm, 316 parts (48 on the bottom side), 216 nets.

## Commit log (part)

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2026-06-03 chore: Initialize project IoT-Gateway
    Initial project setup with KiCad template structure
2026-06-10 Working on PCB
2026-06-21 Working on first version
2026-06-22 Working on version 1.0
2026-06-22 Working on OS
2026-06-23 Fix broken variant variable
2026-06-24 Add WiFi antenna, add CAN interface
2026-06-24 Working on version 1.0.0
2026-06-24 LoRa packet forwarder working, USB working
2026-06-24 LoRa and WiFi are working
2026-06-25 - Add configuration variable for Zigbee2MQTT and wmbusmeters - Add MQTT support for vmbusmeters - Update documentation
2026-06-25 Aktualisieren von README.md
2026-06-26 Fixining network issues
2026-06-29 Update pin mappings
2026-06-29 Adding level shifter, update documentation
